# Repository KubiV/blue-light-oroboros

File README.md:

# blue-light-oroboros

## Úvod
V této práci se zabýváme vývojem externího světelného LED zdroje pro přístroj Oroboros O2k, který slouží pro vysoce přesné monitorování respirační aktivity biologických a biochemických vzorků.

*Stroj Oroboros O2k s nasazeným světlem*

## Problém
Stávající světelné zdroje pro Oroboros O2k jsou drahé a u starších modelů již nedostupné. Naším cílem bylo navrhnout cenově dostupnou a modulární alternativu, která by umožnila precizní experimentální podmínky.

## Materiál a metody
Náš systém zahrnuje řídící box s elektronikou založenou na Arduino Leonardo. K ovládání světel je použit rotační enkodér a 3 tlačítka, zatímco desktopová aplikace umožňuje softwarové nastavení PWM signálu (0–255) pro dvě LED diody. LED zdroje s dominantní vlnovou délkou 465 nm jsou integrovány do 3D tištěných pouzder. Experiment proběhl s bilirubinem rozpuštěným v BSA, kdy fotooxidační reakce bilirubinu (na lumirubin a biliverdinové deriváty) vedly k měření spotřeby kyslíku.

*První verze zapojení na nepájivém poli*

*Finální zapojení na prototypové desce*

## Technický popis
Projekt využívá Arduino Leonardo pro řízení dvou LED diod, s PWM regulací a jednoduchým ovládáním pomocí enkodéru a tlačítek. Firmware na řídícím čipu přijímá sériové příkazy pro nastavení jasu jednotlivých LED. Uživatelská aplikace, vyvinutá v Pythonu s knihovnou PyQt5, umožňuje ovládání LED přes grafické rozhraní se samostatnými i synchronizovanými časovači, sliderem a textovým vstupem. Modularita hardwaru umožňuje rozšíření o další zdroje s různými vlnovými délkami.

*Finální box s možností připojení dvou LED světel*

## Výsledky
Vyvinutý systém umožňuje individuální i synchronizované ovládání obou LED světel, včetně časovačů pro přesné nastavení trvání osvětlení. Software poskytuje interaktivní slider, tlačítka předvoleb a možnost zadat konkrétní hodnoty jasu, což vede ke spolehlivému monitorování spotřeby kyslíku a k analýze fotoproduktů.

## Závěr a diskuse
Náš LED zdroj představuje praktickou a ekonomickou alternativu k původním řešením. Jeho modularita umožňuje rozšíření o další světelné zdroje s různými vlnovými délkami. Experiment s bilirubinem ukázal, že naše řešení umožňuje precizní kontrolu osvětlení, což výrazně ovlivňuje experimentální podmínky a kvalitu dat.

## Technická dokumentace

### Struktura projektu
```
blue-light-oroboros/
├── requirements.txt         # Seznam závislostí pro Python aplikaci a generování grafů
├── Software/
│   └── SW_Dual/
│       ├── led/
│       │   └── led.ino      # Arduino firmware pro ovládání LED
│       └── led2.py          # Python aplikace pro ovládání LED
├── Data/
│   ├── Graph1/
│   │   └── graph4.py        # Vizualizace dat - koncentrace BR
│   ├── Graph2/
│   │   └── graph1.py        # Vizualizace dat - různé intenzity světla
│   ├── Graph3/
│   │   └── graph1.py        # Vizualizace dat - porovnání BR a LR v různých vzorcích
│   └── Graph4/
│       └── graph1.py        # Vizualizace dat - závislost intenzity a PWM
├── CAD/
│   ├── 3D print/
│   │   └── BlueLight.3mf    # Detaily pro tisk ve formátu 3MF (LED světlo)
│   └── BlueLight.step       # Zdrojový STEP soubor pro 3D model (LED světlo)
└── Docs/
  └── Instrukce.pdf          # Instrukce pro sestavení kryu LED světla
```

### Popis komponent

#### Arduino Firmware (led.ino)
- Ovládání dvou LED zdrojů přes PWM (piny 11 a 3)
- Implementace rotačního enkodéru pro manuální ovládání jasu
- Tři tlačítka pro rychlé předvolby (vypnuto, přepínání LED, maximum)
- Sériová komunikace pro příjem příkazů z PC aplikace

#### Python Aplikace (led2.py)
- GUI aplikace vytvořená v PyQt5
- Ovládání jasu LED pomocí slideru nebo přímého zadání hodnoty
- Implementace časovačů pro každou LED
- Možnost synchronizace obou LED
- Sériová komunikace s Arduino kontrolérem

*Uživatelské rozhraní aplikace pro ovládání LED světel*

#### Vizualizační skripty
- **graph1.py**: Analýza a vizualizace dat pro různé intenzity osvětlení
- **graph4.py**: Analýza a vizualizace dat pro různé koncentrace bilirubinu

### Hardware
- Arduino Leonardo
- 2x LED dioda (465 nm)
- Rotační enkodér
- 3x tlačítko
- 3D tištěná pouzdra pro LED a řídící box

### Komunikační protokol
- **Příkazy pro Arduino:**
  - `SET1:xxx` - Nastavení jasu LED 1 (xxx = 0-255)
  - `SET2:xxx` - Nastavení jasu LED 2 (xxx = 0-255)
- **Odpovědi z Arduina:**
  - `BRIGHTNESS1:xxx` - Aktuální jas LED 1
  - `BRIGHTNESS2:xxx` - Aktuální jas LED 2

## Literatura
- Oroboros Instruments: https://wiki.oroboros.at/index.php/PB_Light_Source
- Nature Article: https://www.nature.com/articles/s41598-020-61280-z
- Pediatrics: https://publications.aap.org/pediatrics/article/114/1/297/64771/Management-of-Hyperbilirubinemia-in-the-Newborn?autologincheck=redirected

## Poděkování
Děkujeme všem, kteří přispěli svými odbornými znalostmi a podporou k úspěšnému vývoji tohoto projektu.

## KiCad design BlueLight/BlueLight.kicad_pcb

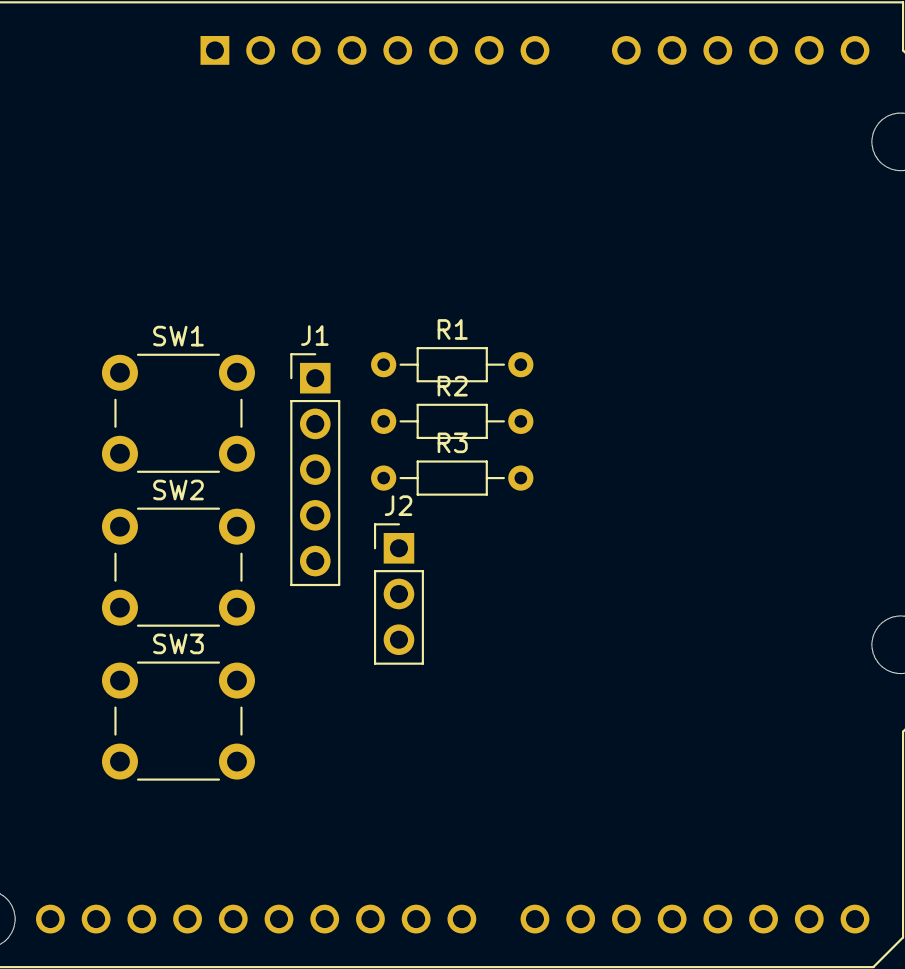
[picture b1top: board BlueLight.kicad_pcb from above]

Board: 2 copper layers, 9 parts (0 on the bottom side), 9 nets, no tracks yet.

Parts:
A1: Arduino_Leonardo; Arduino_UNO_R3_WithMountingHoles
J1: Rotary Encoder; PinHeader_1x05_P2.54mm_Vertical
J2: LED; PinHeader_1x03_P2.54mm_Vertical
R1, R2, R3: 10k; R_Axial_DIN0204_L3.6mm_D1.6mm_P7.62mm_Horizontal
SW1, SW2, SW3: SW_Push_Dual; SW_PUSH_6mm

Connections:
+5V: A1.5 (+5V), J1.4, J2.2, SW1.1, SW2.1, SW3.1
/BTN0: A1.22 (D7), J1.3
/BTN1: A1.23 (D8), R1.1, SW1.2
/BTN2: A1.24 (D9), R2.1, SW2.2
/BTN3: A1.25 (D10), R3.1, SW3.2
/CLK: A1.28 (D13), J1.1
/DTR: A1.27 (D12), J1.2
/LED: A1.26 (D11), J2.3
GND: A1.6 (GND), A1.7 (GND), A1.29 (GND), J1.5, J2.1, R1.2, R2.2, R3.2

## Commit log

2025-01-03 init
2025-01-07 new app
    timer added
2025-01-07 cad
    cad files added
2025-01-09 adjustements
2025-01-09 exe app file added
2025-01-17 doule version init
2025-01-17 dual app
2025-01-17 dual app v1
2025-01-17 double app
2025-01-17 double app exe
2025-01-18 double app exee
2025-01-18 foto and docs
2025-03-16 readme + data
2025-04-04 end products graph
2025-04-04 edit
2025-04-04 typo
2025-04-08 foto
2025-04-08 folder update
2025-04-08 case sensitive
2025-04-09 new graph
2025-04-10 images
2025-04-10 requirements update
2025-04-10 readme
